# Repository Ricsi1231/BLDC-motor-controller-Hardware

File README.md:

## EmbedCore - BLDC Motor Controller

EmbedCore motor controller is a high-power brushless motor controller. It was specifically designed to be integrated in Autonomus Mobile Robot wheel actuators. Motor controller can be intagreted to other applications.
BLDC Motor Controller is also my final thesis work at Subotica Tech - College of Applied Sciences.

***

## SPECIFICATIONS

| Parameter | EmbedCore BLDC Controller V1.0 | 
| --- | --- |
| Voltage Input | 12-44V |
| Peak Electrical Power | TBD |
| Mass | TBD |
| Peak Phase Current | 100A |
| Communication | 5Mbps CAN-FD & RS485 |
| Cooling | 12V Fan |
| Positioning | 2x Onboard 14-bit Encoders |
| Control rate | 15-30kHz |
| PWM Switching Rate | 15-60kHz |
| MCU | STM32G474 |
| Dimensions | 67 x 76.5mm |

***

## DIRECTORY STRUCTURE

```
BLDC motor controller
├── 3D                             # 3D render pictures of the board
├── Datasheets                     # Main component datasheets
├── Specification                  # Specification description about the project
├── Documentation
│   |── Schematic                  # PDF Schematic
│   |── PCB                        # PCB Documentation in PDF
│   |── Computations               # Computations for the components
├── lib
    |── 3d_models                  # Component 3D models
    |── lib_fp                     # Footprint libraries
    |── lib_sym                    # Symbol libraries
├── Logos                          # EmbedCore logo
├── Manufacturing
│   |── Gerber                     # Gerbers files
│   |── BOOM                       # Bill of matirials
│   |── Component Postions         # Components positions for PCB assembly
│   |── Drill files                # Drill files for assembly
├── Templates                      # Title block templates
```

## FIRMWARE

Associated firmware is in [BLDC Motor Controller - Firmware](https://gitlab.com/autonomus-mobile-robot/firmware) repository.

## Lisence
The project is under Apache License 2.0 lisence.

## Support
If you need help about this board, you can reach me at this mail: embedcore7@gmail.com

***

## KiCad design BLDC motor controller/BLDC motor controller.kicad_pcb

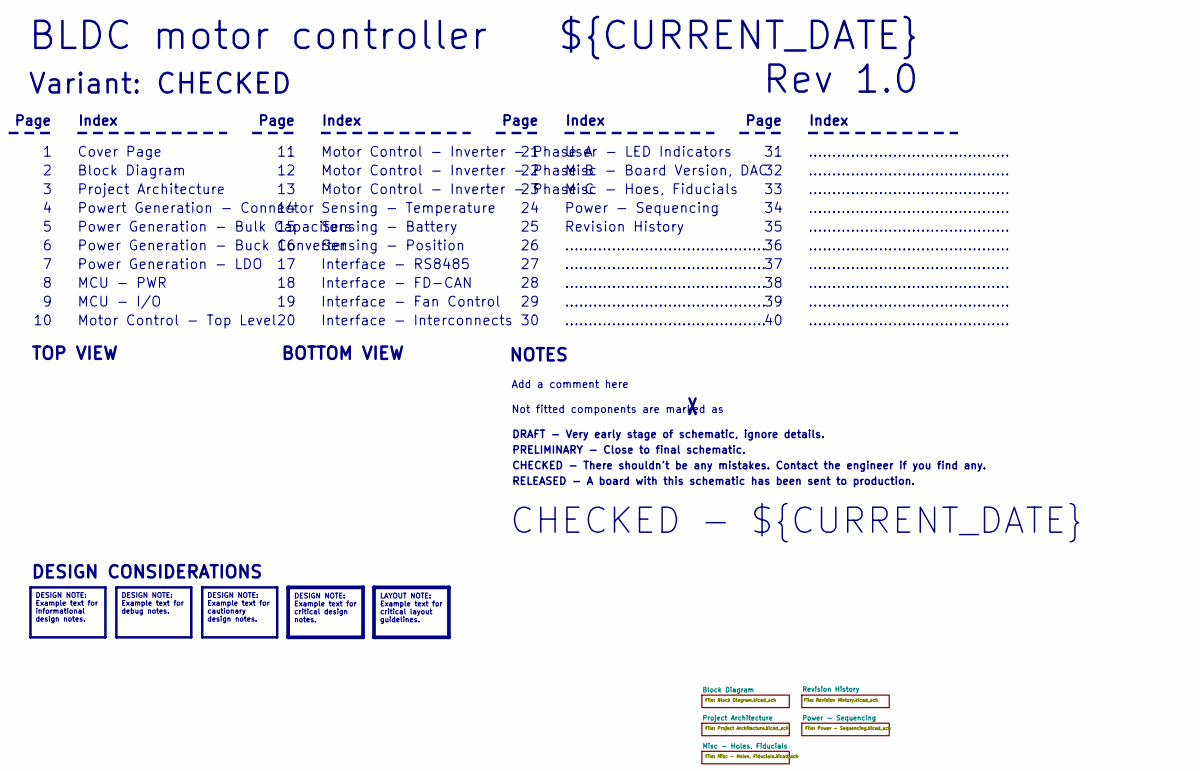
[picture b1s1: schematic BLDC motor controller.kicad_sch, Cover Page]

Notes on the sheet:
BOTTOM VIEW
Misc - Hoes, Fiducials
RELEASED - A board with this schematic has been sent to production.
Page
TOP VIEW
Motor Control - Top Level
MCU - I/O
MCU - PWR
Sensing - Position
Not fitted components are marked as
...........................................
Index
Motor Control - Inverter - Phase C
PRELIMINARY - Close to final schematic.
CHECKED - ${CURRENT_DATE}
Powert Generation - Connector
${CURRENT_DATE}
Variant: CHECKED
Rev 1.0
Power - Sequencing
Misc - Board Version, DAC
Power Generation - Bulk Capacitors
Interface - Fan Control
Motor Control - Inverter - Phase A
Interface - RS8485
Sensing - Battery
BLDC motor controller
DRAFT - Very early stage of schematic, ignore details.
Sensing - Temperature
Power Generation - Buck Converter
Block Diagram
Revision History
Add a comment here
Interface - FD-CAN
Interface - Interconnects
Cover Page
NOTES
Motor Control - Inverter - Phase B
Project Architecture
CHECKED - There shouldn't be any mistakes. Contact the engineer if you find any.

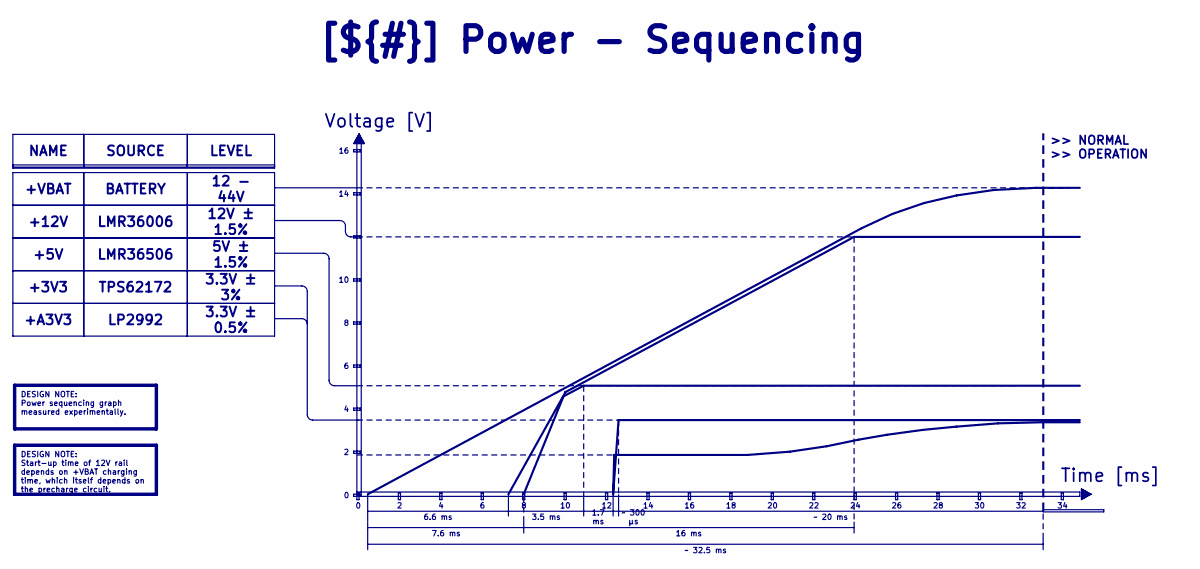
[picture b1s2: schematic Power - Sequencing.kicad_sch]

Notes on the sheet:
Time [ms]
Voltage [V]
>> NORMAL >> OPERATION
~ 20 ms
+12V
3.3V ± 0.5%
LMR36006
16 ms
12V ± 1.5%
+5V
LP2992
TPS62172
6.6 ms
LMR36506
NAME
DESIGN NOTE: Start-up time of 12V rail depends on +VBAT charging time, which itself depends on the precharge circuit.
12 - 44V
DESIGN NOTE: Power sequencing graph measured experimentally.
SOURCE
[${#}] ${TITLE}
LEVEL
+VBAT
+A3V3
BATTERY
5V ± 1.5%
+3V3
7.6 ms
~ 300 μs
3.3V ± 3%
3.5 ms
1.7 ms
~ 32.5 ms

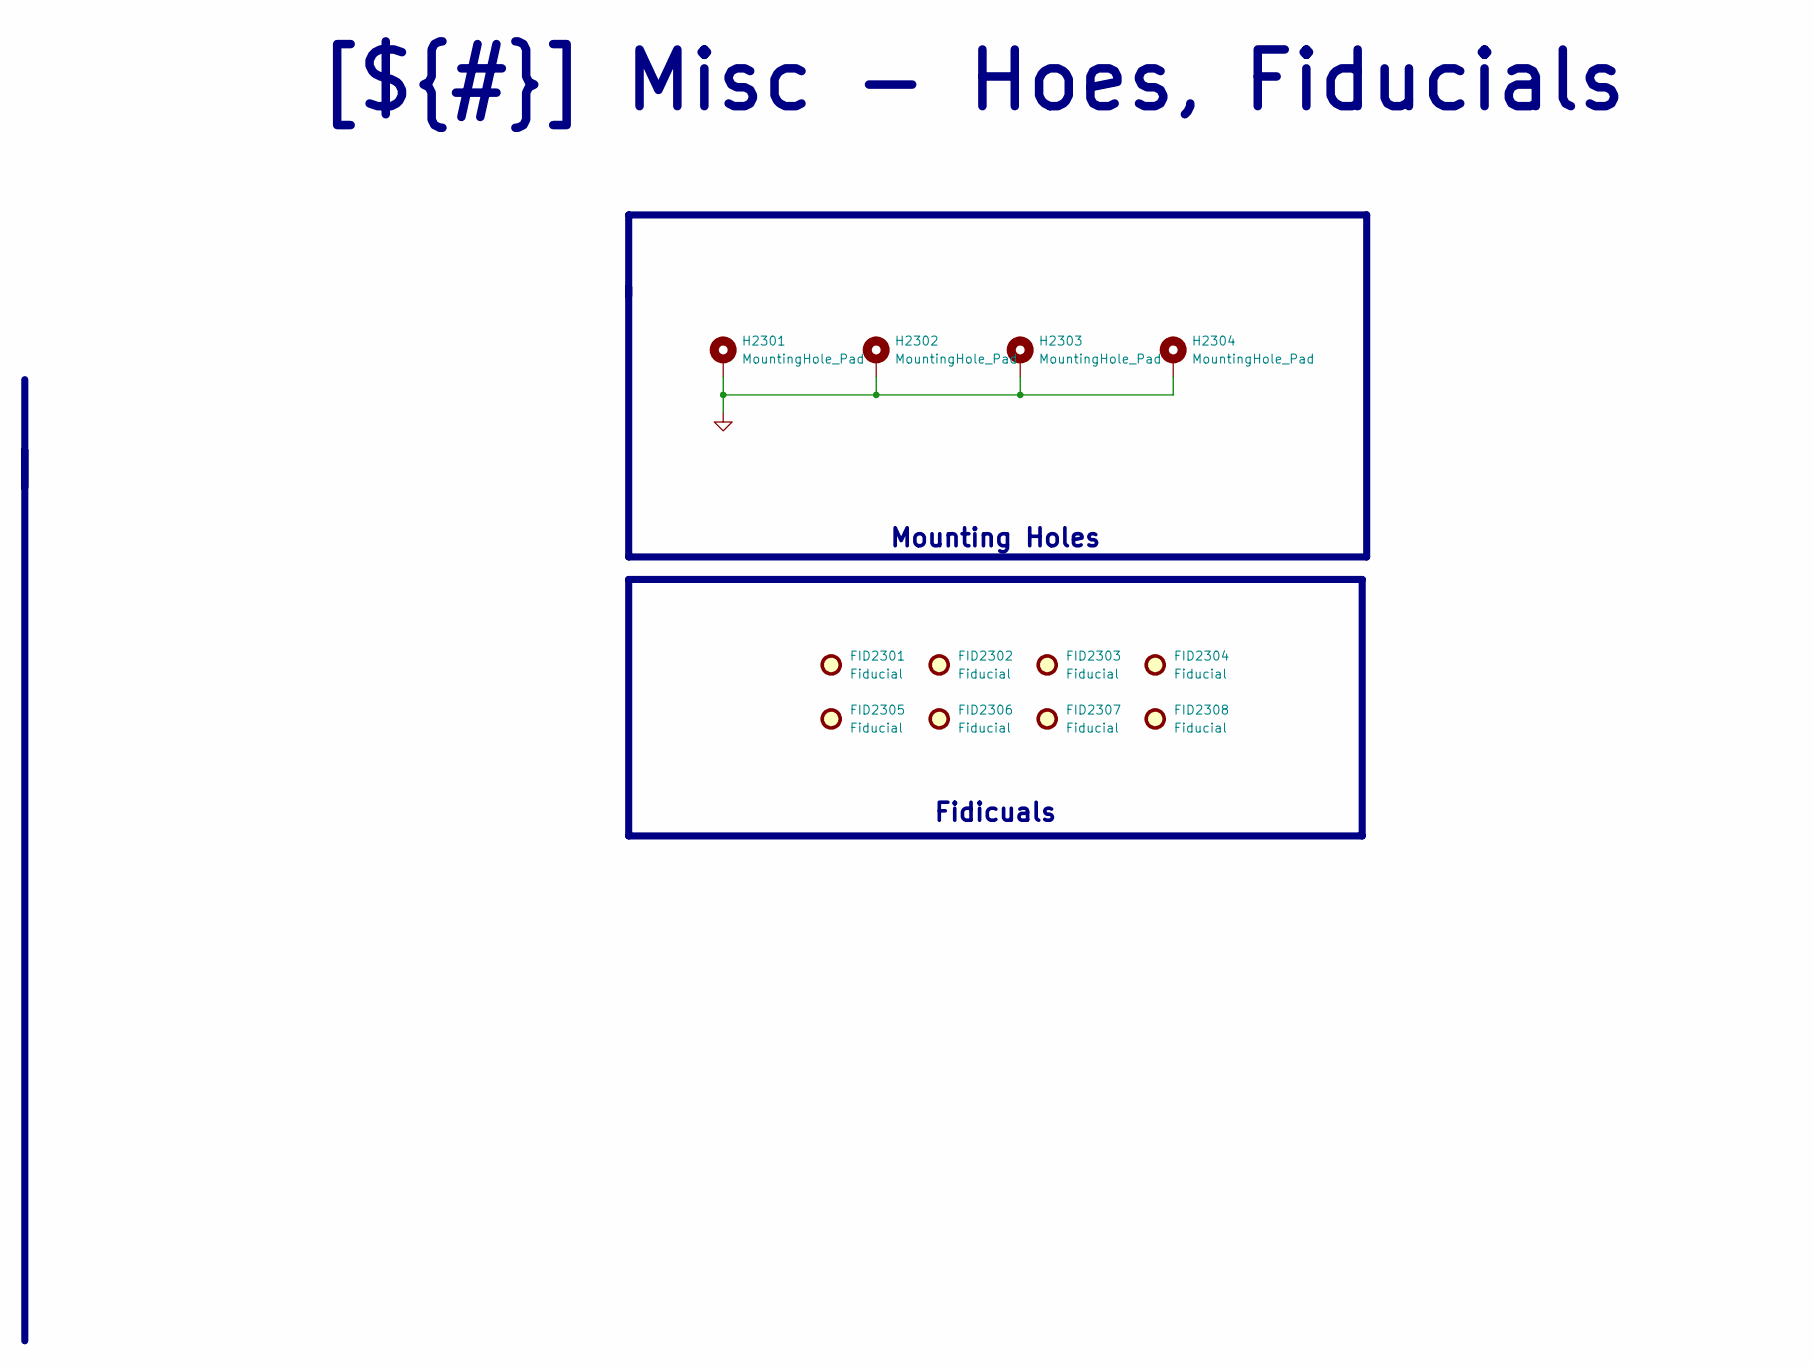
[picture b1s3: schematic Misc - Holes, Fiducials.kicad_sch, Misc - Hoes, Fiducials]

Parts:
FID2301, FID2302, FID2303, FID2304, FID2305, FID2306, FID2307, FID2308: Fiducial; Fiducial_0.5mm_Mask1.5mm
H2301, H2302, H2303, H2304: MountingHole_Pad; MountingHole_3mm_Pad_Via

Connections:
GND: H2301.1, H2302.1, H2303.1, H2304.1; also elsewhere on the board

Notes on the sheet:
Fidicuals
[${#}] ${TITLE}
Mounting Holes

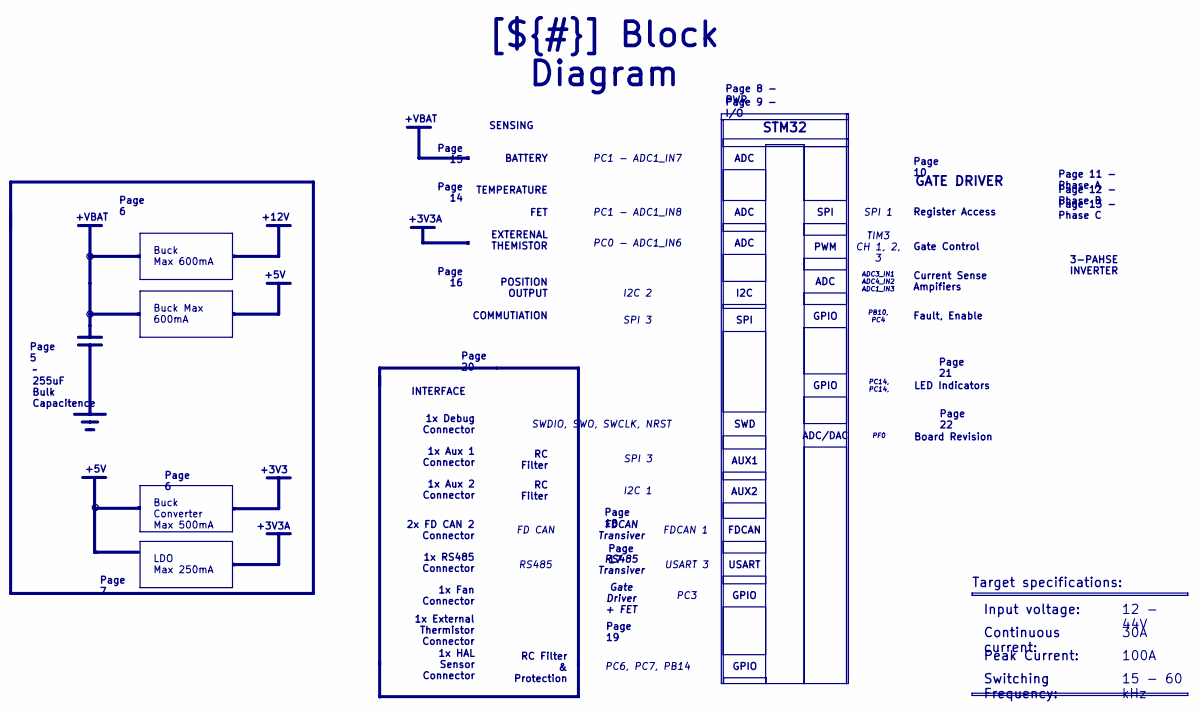
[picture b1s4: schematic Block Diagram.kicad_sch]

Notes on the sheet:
+3V3
+12V
+5V
+3V3A
+VBAT
1x Aux 2 Connector
LED Indicators
1x RS485 Connector
Page 21
Peak Current:
Buck Max 600mA
ADC
1x Aux 1 Connector
Page 19
SWDIO, SWO, SWCLK, NRST
USART
~ 255uF Bulk Capacitence
1x Debug Connector
RS485
Continuous current:
RS485 Transiver
PC1 - ADC1_IN8
2x FD CAN 2 Connector
STM32
SPI 3
Page 12 - Phase B
1x External Thermistor Connector
Page 10
SPI 1
Input voltage:
PC1 - ADC1_IN7
15 - 60 kHz
30A
AUX2
POSITION OUTPUT COMMUTIATION
ADC3_IN1 ADC4_IN2 ADC1_IN3
I2C 2
FD CAN
GPIO
GATE DRIVER

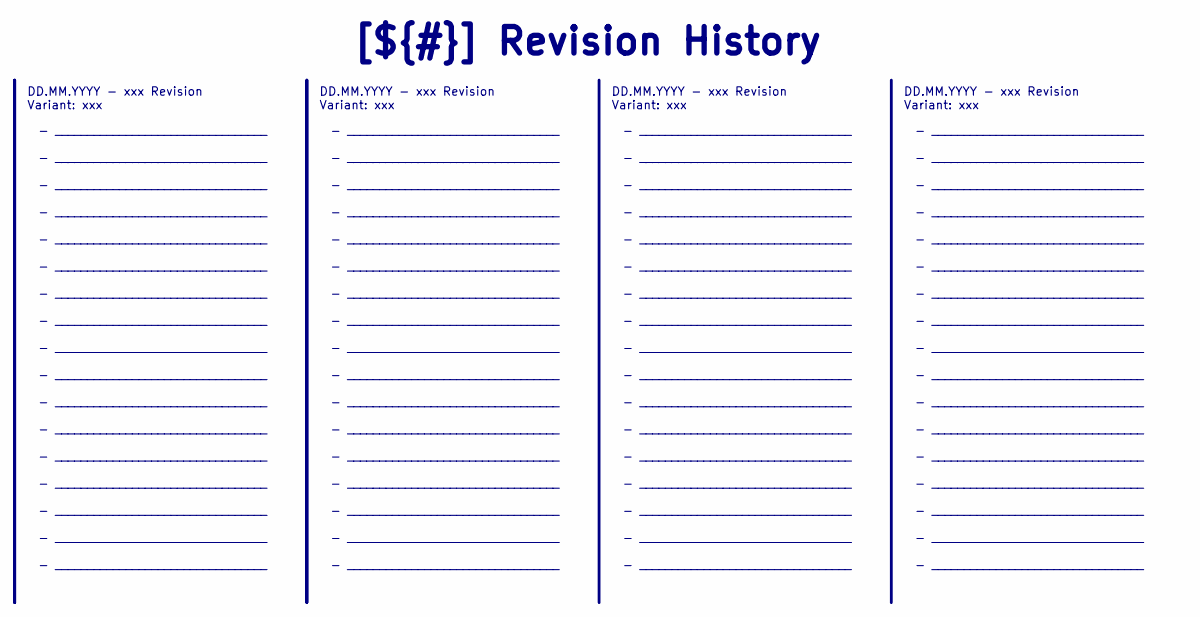
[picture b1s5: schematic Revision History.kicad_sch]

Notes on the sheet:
- _________________________________ - _________________________________ - _________________________________ - _________________________________ - _________________________________ - _________________________________ - _________________________________ - _________________________________ - _________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
DD.MM.YYYY - xxx Revision Variant: xxx
[${#}] ${TITLE}

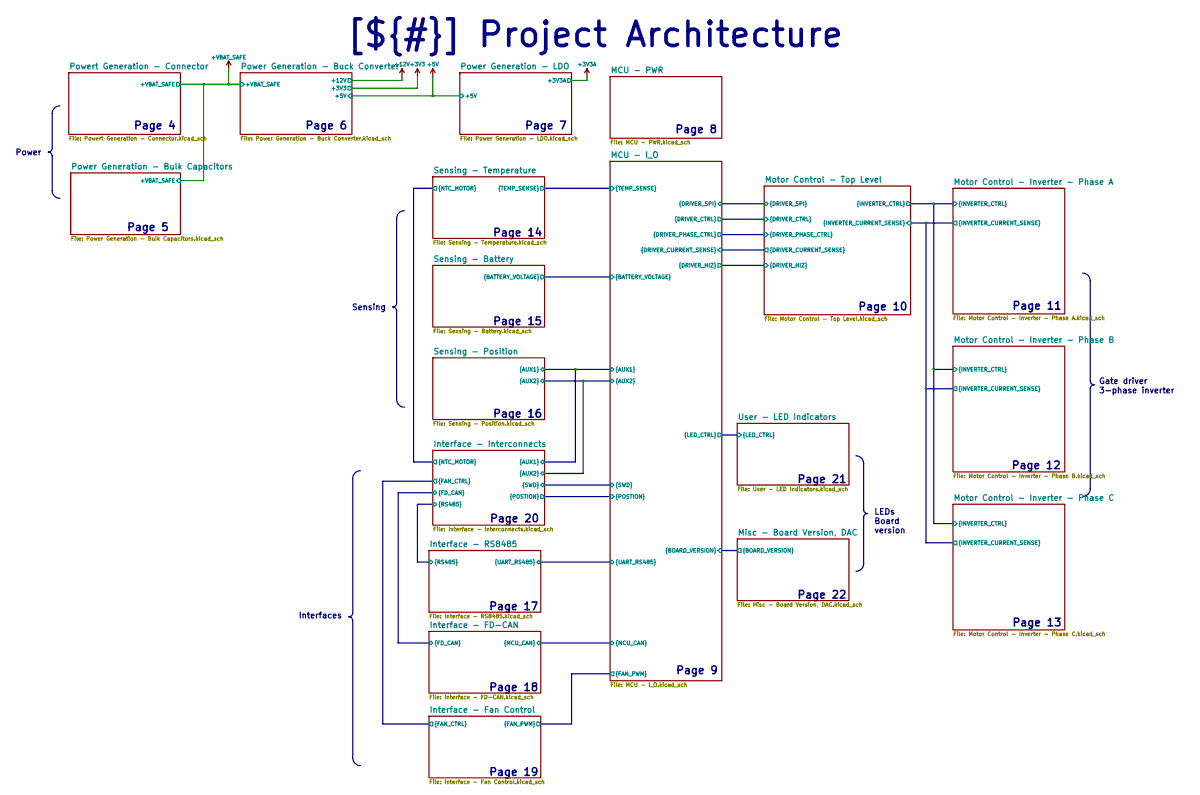
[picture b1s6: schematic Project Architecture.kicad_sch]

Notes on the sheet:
Page 13
Page 16
Page 19
Page 8
Page 22
Page 9
Page 5
Page 11
Page 21
Page 12
Page 10
Page 14
Page 7
Page 4
Page 6
Page 17
Page 15
Page 18
Page 20
Sensing
Interfaces
Gate driver 3-phase inverter
LEDs Board version
[${#}] ${TITLE}
Power

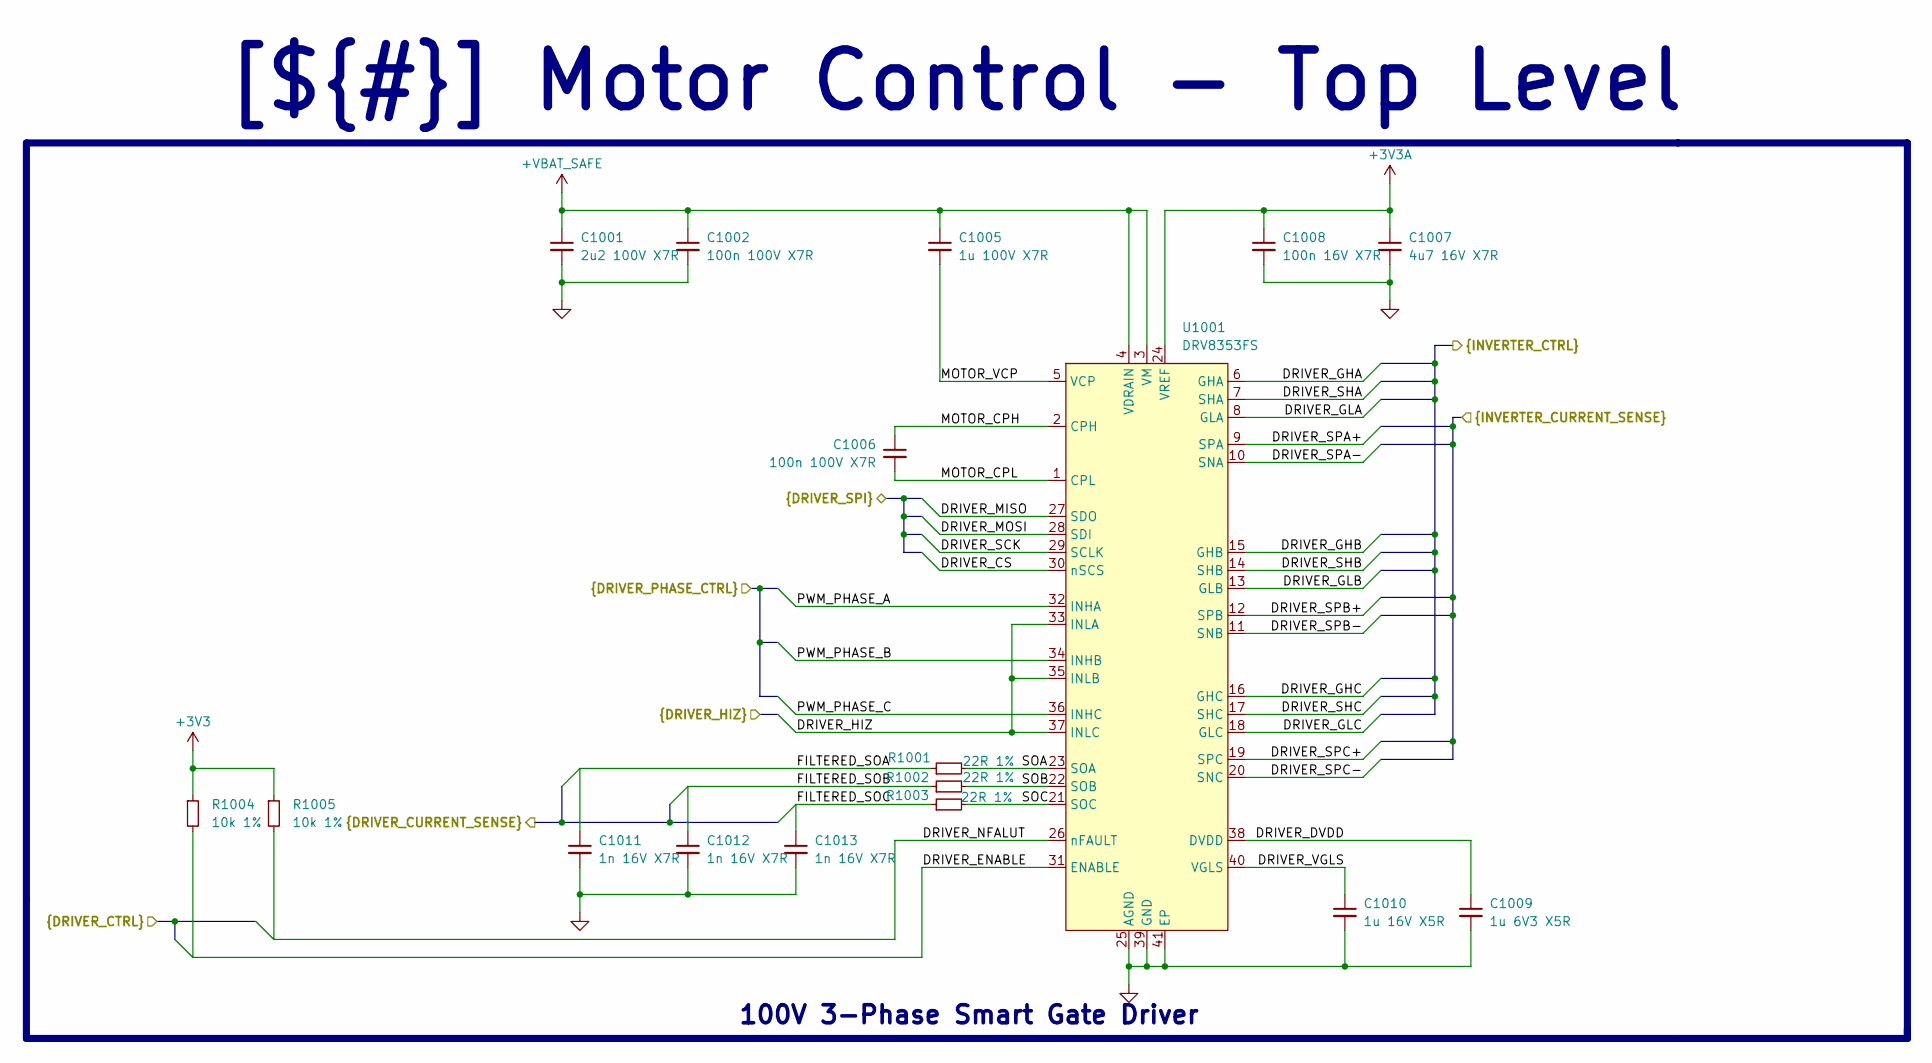
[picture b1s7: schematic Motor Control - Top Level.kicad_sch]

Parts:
C1001: 2u2 100V X7R; C_0805_2012Metric; Manufacturer Part Number CGA4J1X7R2A225K125AC
C1002, C1006: 100n 100V X7R; C_0603_1608Metric; Manufacturer Part Number KAF15BR72A104KT
C1005: 1u 100V X7R; C_0805_2012Metric; Manufacturer Part Number 08051C105K4T2A
C1007: 4u7 16V X7R; C_0603_1608Metric; Manufacturer Part Number GRM188Z71C475KE21D
C1008: 100n 16V X7R; C_0402_1005Metric; Manufacturer Part Number C1005X7R1C104K050BC
C1009: 1u 6V3 X5R; C_0402_1005Metric; Manufacturer Part Number CL05B105KQ5QNWC
C1010: 1u 16V X5R; C_0603_1608Metric; Manufacturer Part Number EMK107B7105KA8T
C1011, C1012, C1013: 1n 16V X7R; C_0402_1005Metric; Manufacturer Part Number GRM155R71C103KA01J
R1001, R1002, R1003: 22R 1%; R_0402_1005Metric; Manufacturer Part Number ERJ-PA2F22R0X
R1004, R1005: 10k 1%; R_0402_1005Metric; Manufacturer Part Number ERJ-PA2F1002X
U1001: DRV8353FS; QFN50P600X600X80-41N-D; Manufacturer Part Number DRV8353FSRTAR

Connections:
+3V3: R1004.1, R1005.1; also elsewhere on the board
+3V3A: C1007.1, C1008.1, U1001.24 (VREF); also elsewhere on the board
+VBAT_SAFE: C1001.1, C1002.1, C1005.1, U1001.3 (VM), U1001.4 (VDRAIN); also elsewhere on the board
/Project Architecture/MCU - I_O/DRIVER_CS: U1001.30 (nSCS); also elsewhere on the board
/Project Architecture/MCU - I_O/DRIVER_ENABLE: R1004.2, U1001.31 (ENABLE); also elsewhere on the board
/Project Architecture/MCU - I_O/DRIVER_HIZ: U1001.33 (INLA), U1001.35 (INLB), U1001.37 (INLC); also elsewhere on the board
/Project Architecture/MCU - I_O/DRIVER_MISO: U1001.27 (SDO); also elsewhere on the board
/Project Architecture/MCU - I_O/DRIVER_MOSI: U1001.28 (SDI); also elsewhere on the board
/Project Architecture/MCU - I_O/DRIVER_NFALUT: R1005.2, U1001.26 (nFAULT); also elsewhere on the board
/Project Architecture/MCU - I_O/DRIVER_SCK: U1001.29 (SCLK); also elsewhere on the board
/Project Architecture/MCU - I_O/FILTERED_SOA: C1011.1, R1001.1; also elsewhere on the board
/Project Architecture/MCU - I_O/FILTERED_SOB: C1012.1, R1002.1; also elsewhere on the board
/Project Architecture/MCU - I_O/FILTERED_SOC: C1013.1, R1003.1; also elsewhere on the board
/Project Architecture/MCU - I_O/PWM_PHASE_A: U1001.32 (INHA); also elsewhere on the board
/Project Architecture/MCU - I_O/PWM_PHASE_B: U1001.34 (INHB); also elsewhere on the board
/Project Architecture/MCU - I_O/PWM_PHASE_C: U1001.36 (INHC); also elsewhere on the board
/Project Architecture/Motor Control - Inverter - Phase A/DRIVER_GHA: U1001.6 (GHA); also elsewhere on the board
/Project Architecture/Motor Control - Inverter - Phase A/DRIVER_GHB: U1001.15 (GHB); also elsewhere on the board
/Project Architecture/Motor Control - Inverter - Phase A/DRIVER_GHC: U1001.16 (GHC); also elsewhere on the board
/Project Architecture/Motor Control - Inverter - Phase A/DRIVER_GLA: U1001.8 (GLA); also elsewhere on the board
/Project Architecture/Motor Control - Inverter - Phase A/DRIVER_GLB: U1001.13 (GLB); also elsewhere on the board
/Project Architecture/Motor Control - Inverter - Phase A/DRIVER_GLC: U1001.18 (GLC); also elsewhere on the board
/Project Architecture/Motor Control - Inverter - Phase A/DRIVER_SHA: U1001.7 (SHA); also elsewhere on the board
/Project Architecture/Motor Control - Inverter - Phase A/DRIVER_SHB: U1001.14 (SHB); also elsewhere on the board
/Project Architecture/Motor Control - Inverter - Phase A/DRIVER_SHC: U1001.17 (SHC); also elsewhere on the board
/Project Architecture/Motor Control - Inverter - Phase A/DRIVER_SPA+: U1001.9 (SPA); also elsewhere on the board
/Project Architecture/Motor Control - Inverter - Phase A/DRIVER_SPA-: U1001.10 (SNA); also elsewhere on the board
/Project Architecture/Motor Control - Inverter - Phase A/DRIVER_SPB+: U1001.12 (SPB); also elsewhere on the board
/Project Architecture/Motor Control - Inverter - Phase A/DRIVER_SPB-: U1001.11 (SNB); also elsewhere on the board
/Project Architecture/Motor Control - Inverter - Phase A/DRIVER_SPC+: U1001.19 (SPC); also elsewhere on the board
/Project Architecture/Motor Control - Inverter - Phase A/DRIVER_SPC-: U1001.20 (SNC); also elsewhere on the board
/Project Architecture/Motor Control - Top Level/DRIVER_DVDD: C1009.1, U1001.38 (DVDD)
/Project Architecture/Motor Control - Top Level/DRIVER_VGLS: C1010.1, U1001.40 (VGLS)
/Project Architecture/Motor Control - Top Level/MOTOR_CPH: C1006.1, U1001.2 (CPH)
/Project Architecture/Motor Control - Top Level/MOTOR_CPL: C1006.2, U1001.1 (CPL)
/Project Architecture/Motor Control - Top Level/MOTOR_VCP: C1005.2, U1001.5 (VCP)
/Project Architecture/Motor Control - Top Level/SOA: R1001.2, U1001.23 (SOA)
/Project Architecture/Motor Control - Top Level/SOB: R1002.2, U1001.22 (SOB)
/Project Architecture/Motor Control - Top Level/SOC: R1003.2, U1001.21 (SOC)
GND: C1001.2, C1002.2, C1007.2, C1008.2, C1009.2, C1010.2, C1011.2, C1012.2, C1013.2, U1001.25 (AGND), U1001.39 (GND), U1001.41 (EP); also elsewhere on the board

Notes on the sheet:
[${#}] Motor Control - Top Level
100V 3-Phase Smart Gate Driver

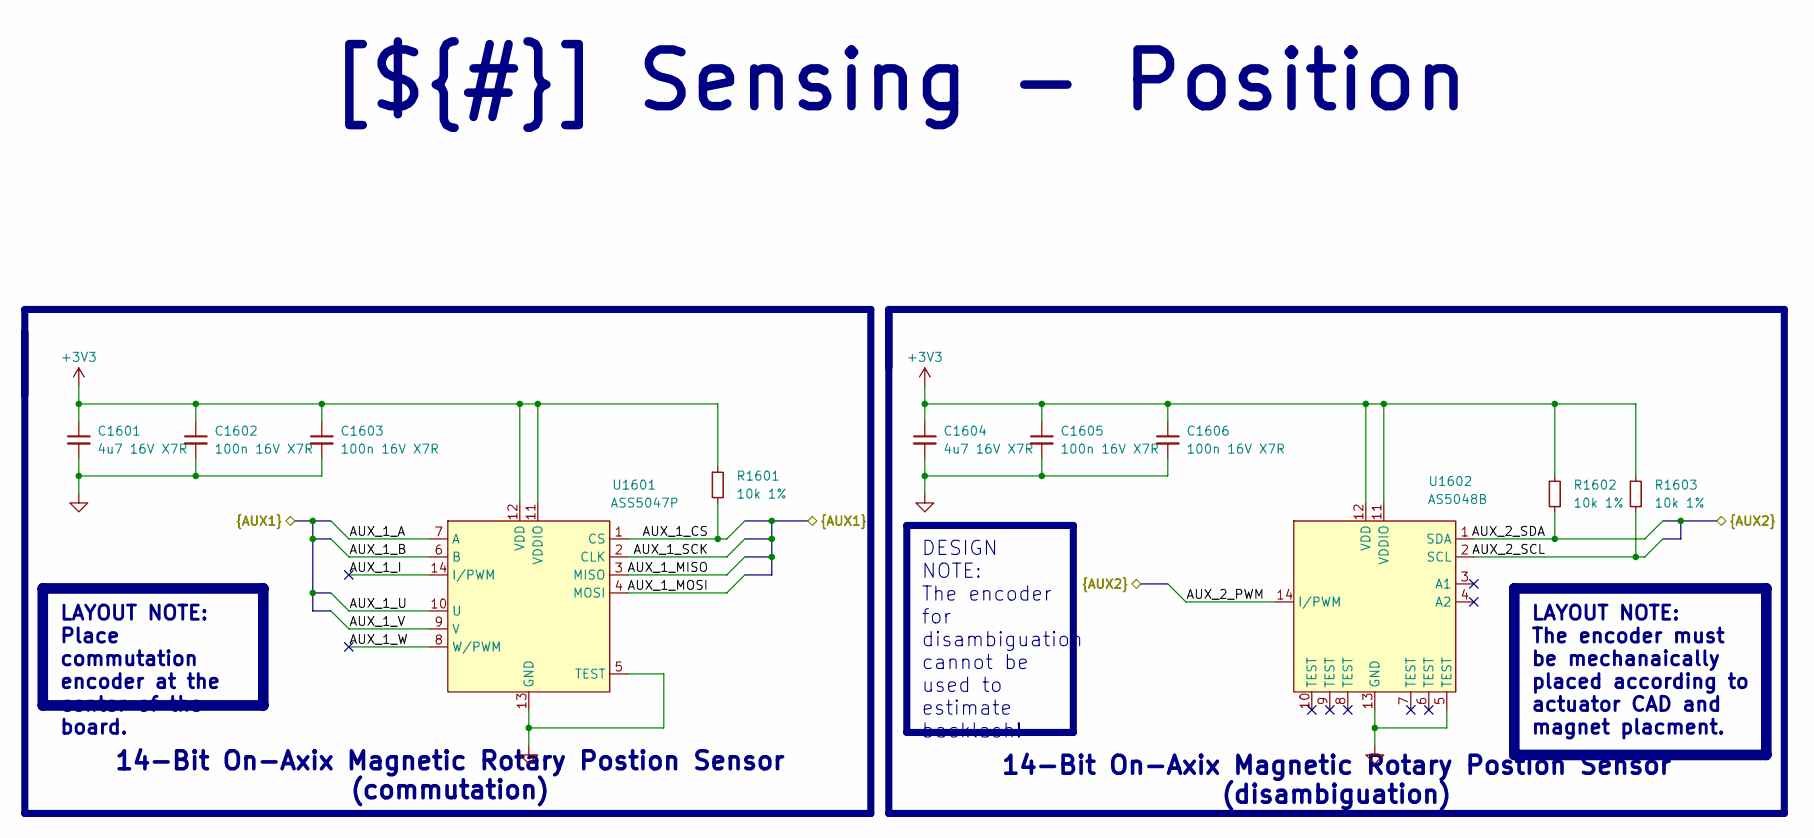
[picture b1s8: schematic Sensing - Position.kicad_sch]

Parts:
C1601, C1604: 4u7 16V X7R; C_0603_1608Metric; Manufacturer Part Number GRM188Z71C475KE21D
C1602, C1603, C1605, C1606: 100n 16V X7R; C_0402_1005Metric; Manufacturer Part Number C1005X7R1C104K050BC
R1601, R1602, R1603: 10k 1%; R_0402_1005Metric; Manufacturer Part Number ERJ-PA2F1002X
U1601: ASS5047P; SOP65P640X120-14N; Manufacturer Part Number AS5047P-ATSM
U1602: AS5048B; SOP65P640X120-14N; Manufacturer Part Number AS5048B-HTSP

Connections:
+3V3: C1601.1, C1602.1, C1603.1, C1604.1, C1605.1, C1606.1, R1601.1, R1602.1, R1603.1, U1601.11 (VDDIO), U1601.12 (VDD), U1602.11 (VDDIO), U1602.12 (VDD); also elsewhere on the board
/Project Architecture/Interface - Interconnects/AUX_1_A: U1601.7 (A); also elsewhere on the board
/Project Architecture/Interface - Interconnects/AUX_1_B: U1601.6 (B); also elsewhere on the board
/Project Architecture/Interface - Interconnects/AUX_1_CS: R1601.2, U1601.1 (CS); also elsewhere on the board
/Project Architecture/Interface - Interconnects/AUX_1_I: U1601.14 (I/PWM); also elsewhere on the board
/Project Architecture/Interface - Interconnects/AUX_1_MISO: U1601.3 (MISO); also elsewhere on the board
/Project Architecture/Interface - Interconnects/AUX_1_MOSI: U1601.4 (MOSI); also elsewhere on the board
/Project Architecture/Interface - Interconnects/AUX_1_SCK: U1601.2 (CLK); also elsewhere on the board
/Project Architecture/Interface - Interconnects/AUX_1_U: U1601.10 (U); also elsewhere on the board
/Project Architecture/Interface - Interconnects/AUX_1_V: U1601.9 (V); also elsewhere on the board
/Project Architecture/Interface - Interconnects/AUX_1_W: U1601.8 (W/PWM); also elsewhere on the board
/Project Architecture/Interface - Interconnects/AUX_2_PWM: U1602.14 (I/PWM); also elsewhere on the board
/Project Architecture/Interface - Interconnects/AUX_2_SCL: R1603.2, U1602.2 (SCL); also elsewhere on the board
/Project Architecture/Interface - Interconnects/AUX_2_SDA: R1602.2, U1602.1 (SDA); also elsewhere on the board
GND: C1601.2, C1602.2, C1603.2, C1604.2, C1605.2, C1606.2, U1601.5 (TEST), U1601.13 (GND), U1602.5 (TEST), U1602.13 (GND); also elsewhere on the board

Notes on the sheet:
14-Bit On-Axix Magnetic Rotary Postion Sensor (commutation)
[${#}] Sensing - Position
14-Bit On-Axix Magnetic Rotary Postion Sensor (disambiguation)
DESIGN NOTE: The encoder for disambiguation cannot be used to estimate backlash!
LAYOUT NOTE: Place commutation encoder at the center of the board.
LAYOUT NOTE: The encoder must be mechanaically placed according to actuator CAD and magnet placment.

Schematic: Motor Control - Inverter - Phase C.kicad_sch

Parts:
C1301, C1302: 22n 100V X7R; C_0805_2012Metric; Manufacturer Part Number KAM21BR72A223KM
C1304: 100n 100V X7R; C_1206_3216Metric; Manufacturer Part Number 885382208006
C1305: 10u 100V X7R; C_1210_3225Metric; Manufacturer Part Number C3225X7R2A106K250AC
D1301, D1302, D1303: BAT41KFILM; D_SOD-523; Manufacturer Part Number BAT41KFILM
J1301: PHASE_C; Pad_Square_Vias_6.5x6.5mm
NT1301, NT1302, NT1303: DIFF_PAIR; NetTie-2_SMD_Pad0.5mm
Q1301, Q1302: TPW1R306PL,L1Q; SOP_ADVANCE; Manufacturer Part Number TPW1R306PL,L1Q
R1301, R1302: 7R5 1%; R_0603_1608Metric; Manufacturer Part Number ERJ-U03F7R50V
R1303: 0m5 1% 2W; R_2512_6332Metric; Manufacturer Part Number PA2512FKE7W0R005E
R1304, R1305: 22R 1%; R_0805_2012Metric; Manufacturer Part Number ERJ-6ENF22R0V

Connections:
+VBAT_SAFE: C1304.1, C1305.1, Q1301.1 (D), R1304.1; also elsewhere on the board
/Project Architecture/Motor Control - Inverter - Phase A/DRIVER_GHC: D1301.1 (K), R1301.1; also elsewhere on the board
/Project Architecture/Motor Control - Inverter - Phase A/DRIVER_GLC: D1302.1 (K), R1302.1; also elsewhere on the board
/Project Architecture/Motor Control - Inverter - Phase A/DRIVER_SHC: NT1301.2; also elsewhere on the board
/Project Architecture/Motor Control - Inverter - Phase A/DRIVER_SPC+: NT1302.2; also elsewhere on the board
/Project Architecture/Motor Control - Inverter - Phase A/DRIVER_SPC-: NT1303.2; also elsewhere on the board
/Project Architecture/Motor Control - Inverter - Phase C/FET_GHC: D1301.2 (A), Q1301.2 (G), R1301.2
/Project Architecture/Motor Control - Inverter - Phase C/FET_GLC: D1302.2 (A), D1303.1 (K), Q1302.2 (G), R1302.2
/Project Architecture/Motor Control - Inverter - Phase C/PHASE_C: C1301.2, J1301.1, NT1301.1, Q1301.3 (S), Q1302.1 (D), R1305.1
/Project Architecture/Motor Control - Inverter - Phase C/PHASE_C_S: C1302.2, C1304.2, NT1302.1, Q1302.3 (S), R1303.1
GND: C1305.2, D1303.2 (A), NT1303.1, R1303.2; also elsewhere on the board
unnamed: C1301.1, R1304.2
unnamed: C1302.1, R1305.2

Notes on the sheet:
Flexible I/O worked examples
References:
Flexible I/O source configuration
Inverter Phase C
DESIGN NOTE: Low-Side Schottky diodes protect FET's gate against negavtive transients.
DESIGN NOTE: Local bulk and negative bounce tone sppression capacitors.
DESIGN NOTE: Optional RC snubber to reduce ringing.
[13] Motor Control - Inverter - Phase C
DESIGN NOTE: Gate resistor + dischrage diode.

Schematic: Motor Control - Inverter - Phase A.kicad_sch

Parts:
C1101, C1102: 22n 100V X7R; C_0805_2012Metric; Manufacturer Part Number KAM21BR72A223KM
C1103: 100n 100V X7R; C_1206_3216Metric; Manufacturer Part Number 885382208006
C1104: 10u 100V X7R; C_1210_3225Metric; Manufacturer Part Number C3225X7R2A106K250AC
D1101, D1102, D1103: BAT41KFILM; D_SOD-523; Manufacturer Part Number BAT41KFILM
J1101: PHASE_A; Pad_Square_Vias_6.5x6.5mm
NT1101, NT1102, NT1103: DIFF_PAIR; NetTie-2_SMD_Pad0.5mm
Q1101, Q1102: TPW1R306PL,L1Q; SOP_ADVANCE; Manufacturer Part Number TPW1R306PL,L1Q
R1101, R1102: 7R5 1%; R_0603_1608Metric; Manufacturer Part Number ERJ-U03F7R50V
R1103: 0m5 1% 2W; R_2512_6332Metric; Manufacturer Part Number PA2512FKE7W0R005E
R1104, R1105: 22R 1%; R_0805_2012Metric; Manufacturer Part Number ERJ-6ENF22R0V

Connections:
+VBAT_SAFE: C1103.1, C1104.1, Q1101.1 (D), R1104.1; also elsewhere on the board
/Project Architecture/Motor Control - Inverter - Phase A/DRIVER_GHA: D1101.1 (K), R1101.1; also elsewhere on the board
/Project Architecture/Motor Control - Inverter - Phase A/DRIVER_GLA: D1102.1 (K), R1102.1; also elsewhere on the board
/Project Architecture/Motor Control - Inverter - Phase A/DRIVER_SHA: NT1101.2; also elsewhere on the board
/Project Architecture/Motor Control - Inverter - Phase A/DRIVER_SPA+: NT1102.2; also elsewhere on the board
/Project Architecture/Motor Control - Inverter - Phase A/DRIVER_SPA-: NT1103.2; also elsewhere on the board
/Project Architecture/Motor Control - Inverter - Phase A/FET_GHA: D1101.2 (A), Q1101.2 (G), R1101.2
/Project Architecture/Motor Control - Inverter - Phase A/FET_GLA: D1102.2 (A), D1103.1 (K), Q1102.2 (G), R1102.2
/Project Architecture/Motor Control - Inverter - Phase A/PHASE_A: C1101.2, J1101.1, NT1101.1, Q1101.3 (S), Q1102.1 (D), R1105.1
/Project Architecture/Motor Control - Inverter - Phase A/PHASE_A_S: C1102.2, C1103.2, NT1102.1, Q1102.3 (S), R1103.1
GND: C1104.2, D1103.2 (A), NT1103.1, R1103.2; also elsewhere on the board
unnamed: C1101.1, R1104.2
unnamed: C1102.1, R1105.2

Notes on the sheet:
Flexible I/O worked examples
References:
Flexible I/O source configuration
DESIGN NOTE: Gate resistor + dischrage diode.
DESIGN NOTE: Low-Side Schottky diodes protect FET's gate against negavtive transients.
[${#}] Motor Control - Inverter - Phase A
DESIGN NOTE: Local bulk and negative bounce tone sppression capacitors.
DESIGN NOTE: Optional RC snubber to reduce ringing.
Inverter Phase A

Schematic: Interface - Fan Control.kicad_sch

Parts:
C1901: 4u7 16V X7R; C_0603_1608Metric; Manufacturer Part Number GRM188Z71C475KE21D
C1902: 100n 16V X7R; C_0402_1005Metric; Manufacturer Part Number C1005X7R1C104K050BC
Q1901: PMV90ENER; SOT-23; Manufacturer Part Number PMV90ENER
R1901: 10R 1%; R_0402_1005Metric; Manufacturer Part Number ERJ-PA2D10R0X
R1902: 10k 1%; R_0402_1005Metric; Manufacturer Part Number ERJ-PA2F1002X
U1901: DGD0216; SOT-23-5; Manufacturer Part Number DGD0216WT-7

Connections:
+3V3: C1901.1, C1902.1, U1901.5 (VCC); also elsewhere on the board
/Project Architecture/Interface - Fan Control/FAN_CONTROL_GATE: Q1901.2 (G), R1901.2, R1902.2
/Project Architecture/Interface - Fan Control/FAN_CONTROL_GATE_R: R1901.1, U1901.4 (OUT)
/Project Architecture/Interface - Fan Control/FAN_CONTROL_IN: U1901.3 (IN); also elsewhere on the board
/Project Architecture/Interface - Fan Control/FAN_CONTROL_PWM: Q1901.1 (D); also elsewhere on the board
GND: C1901.2, C1902.2, Q1901.3 (S), R1902.1, U1901.2 (COM); also elsewhere on the board

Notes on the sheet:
[${#}] Interface - Fan Control
Fan Gate Driver
DESIGN NOTE: Gate resistor should be chosen to slew rate of FET.
DESIGN NOTE: Gate driver is not strictly necsassary fpr hysteresos control, but could be useful for PWM control.

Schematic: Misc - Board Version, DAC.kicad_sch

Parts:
C2201: 100n 100V X7R; C_0603_1608Metric; Manufacturer Part Number KAF15BR72A104KT
R2201: DNP; R_0603_1608Metric; Manufacturer Part Number ERJ-UP3F1003V
R2202: 100k 1%; R_0603_1608Metric

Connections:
+3V3: R2201.2; also elsewhere on the board
/Project Architecture/MCU - I_O/BOARD_VERSION: C2201.1, R2201.1, R2202.2; also elsewhere on the board
GND: C2201.2, R2202.1; also elsewhere on the board

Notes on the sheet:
[${#}] ${TITLE}
Board Version Resistor Divider
DESIGN NOTE: V1 - TOP Resistor 100k BOTTOM DNP. V2 - BOTTOM Resistor 100k TOP DNP.

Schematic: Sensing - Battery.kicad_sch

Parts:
C1501: 100n 100V X7R; C_0603_1608Metric; Manufacturer Part Number KAF15BR72A104KT
R1501: 100k 1%; R_0603_1608Metric; Manufacturer Part Number ERJ-UP3F1003V
R1502: 4k7 1%; R_0603_1608Metric; Manufacturer Part Number ERJ-UP3F4701V

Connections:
+VBAT_SAFE: R1501.2; also elsewhere on the board
/Project Architecture/MCU - I_O/BATTERY_VSENSE: C1501.1, R1501.1, R1502.2; also elsewhere on the board
GND: C1501.2, R1502.1; also elsewhere on the board

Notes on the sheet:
[${#}] Sensing - Battery
DESIGN NOTE: 1/23 temperature stable voltage divider. Use low ppm resistors. 12S: max voltage: 2.19V. 8S: max voltage: 1.95V. 6S: max voltage: 1.46V.
Battery Sensing Voltage Divider

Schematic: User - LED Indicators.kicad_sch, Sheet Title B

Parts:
D2101, D2103: GREEN; LED_0402_1005Metric; Manufacturer Part Number FHD1105P-TR
D2102: RED; LED_0402_1005Metric; Manufacturer Part Number FHR1105P-TR
D2104: YELLOW; LED_0402_1005Metric; Manufacturer Part Number FHY1105P-TR
D2105: BLUE; LED_0402_1005Metric; Manufacturer Part Number 150040BS73220
D2106: ORAGNGE; LED_0402_1005Metric; Manufacturer Part Number SM0402OC
Q2101, Q2102: PMV90ENER; SOT-23; Manufacturer Part Number PMV90ENER
R2101, R2102, R2103, R2104, R2105, R2106, R2107, R2108, R2109, R2110: 10k 1%; R_0402_1005Metric; Manufacturer Part Number ERJ-PA2F1002X

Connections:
+3V3: R2107.2; also elsewhere on the board
+3V3A: R2108.2; also elsewhere on the board
+5V: R2103.2, R2106.2, R2109.2; also elsewhere on the board
+12V: R2110.2; also elsewhere on the board
/Project Architecture/MCU - I_O/LED_DBG_1: R2101.2; also elsewhere on the board
/Project Architecture/MCU - I_O/LED_DBG_2: R2104.2; also elsewhere on the board
/Project Architecture/User - LED Indicators/LED_1_GATE: Q2101.2 (G), R2101.1, R2102.2
/Project Architecture/User - LED Indicators/LED_2_GATE: Q2102.2 (G), R2104.1, R2105.2
/Project Architecture/User - LED Indicators/LED_DBG_1_A: D2101.2 (A), R2103.1
/Project Architecture/User - LED Indicators/LED_DBG_1_K: D2101.1 (K), Q2101.1 (D)
/Project Architecture/User - LED Indicators/LED_DBG_2_A: D2102.2 (A), R2106.1
/Project Architecture/User - LED Indicators/LED_DBG_2_K: D2102.1 (K), Q2102.1 (D)
/Project Architecture/User - LED Indicators/PWR_ON_3V3: D2103.2 (A), R2107.1
/Project Architecture/User - LED Indicators/PWR_ON_3V3A: D2104.2 (A), R2108.1
/Project Architecture/User - LED Indicators/PWR_ON_5V: D2105.2 (A), R2109.1
/Project Architecture/User - LED Indicators/PWR_ON_12V: D2106.2 (A), R2110.1
GND: D2103.1 (K), D2104.1 (K), D2105.1 (K), D2106.1 (K), Q2101.3 (S), Q2102.3 (S), R2102.1, R2105.1; also elsewhere on the board

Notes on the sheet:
Debug LED's
Power On Led's
[${#}] User - LED Indicators

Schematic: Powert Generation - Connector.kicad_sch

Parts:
D401: SMBJ51CA-E3/52; D_SMB; Manufacturer Part Number SMBJ51CA-E3/52
J401: XT60; AMASS_XT60PW-F_1x02_P7.20mm_Horizontal

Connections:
+VBAT_SAFE: D401.1 (K), J401.1; also elsewhere on the board
GND: D401.2 (A), J401.2; also elsewhere on the board

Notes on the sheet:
DESIGN NOTE: Do not hot-plug when powered!
Power Supply Input Protection
LAYOUT NOTE: Place ESD diode near input power connectors.
[${#}] Powert Generation - Connector
LAYOUT NOTE: Keep sufficent clearence between power nets according to ICP-2221.
DESIGN NOTE: Do not exceed absolute maximum rating! Maximum input voltage is 44V (10S).

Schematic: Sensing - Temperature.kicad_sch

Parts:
C1401, C1402: 100n 100V X7R; C_0603_1608Metric; Manufacturer Part Number KAF15BR72A104KT
D1401, D1402: BAT41KFILM; D_SOD-523; Manufacturer Part Number BAT41KFILM
NT1401: NTC_MOT_H; NetTie-2_SMD_Pad0.5mm
NT1402: NTC_MOT_L; NetTie-2_SMD_Pad0.5mm
R1402, R1403: 10k 1%; R_0603_1608Metric; Manufacturer Part Number ERJ-PA3F1002V
TH1401: 47k 1% NTC; R_0603_1608Metric; Manufacturer Part Number NCU18WB473D6SRB

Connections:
+3V3A: D1401.1 (K), D1402.1 (K); also elsewhere on the board
+VBAT_SAFE: NT1401.2, TH1401.1; also elsewhere on the board
/Project Architecture/Interface - Interconnects/TEMP_MOT_H: NT1401.1; also elsewhere on the board
/Project Architecture/Interface - Interconnects/TEMP_MOT_L: NT1402.1; also elsewhere on the board
/Project Architecture/MCU - I_O/SENSE_TEMP_FET: C1401.1, D1401.2 (A), R1402.2, TH1401.2; also elsewhere on the board
/Project Architecture/MCU - I_O/SENSE_TEMP_MOT: C1402.1, D1402.2 (A), NT1402.2, R1403.2; also elsewhere on the board
GND: C1401.2, C1402.2, R1402.1, R1403.1; also elsewhere on the board

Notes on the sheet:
DESIGN NOTE: Nominal B-Constant 4050-4090K.
[${#}] Sensing - Temperature
DESIGN NOTE: Optionally it is possible to add an external thermistor. Not critical for proper operation.
Mosfet and Motor Temperature Sensing
LAYOUT NOTE: NTC's must be placed close and thermally coupled to relevant heat source. Route away from noisy traces.
